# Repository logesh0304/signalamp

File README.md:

View this project on [CADLAB.io](https://cadlab.io/project/27638). 

# signalamp
 Signal amplifier for amplifying weak signals

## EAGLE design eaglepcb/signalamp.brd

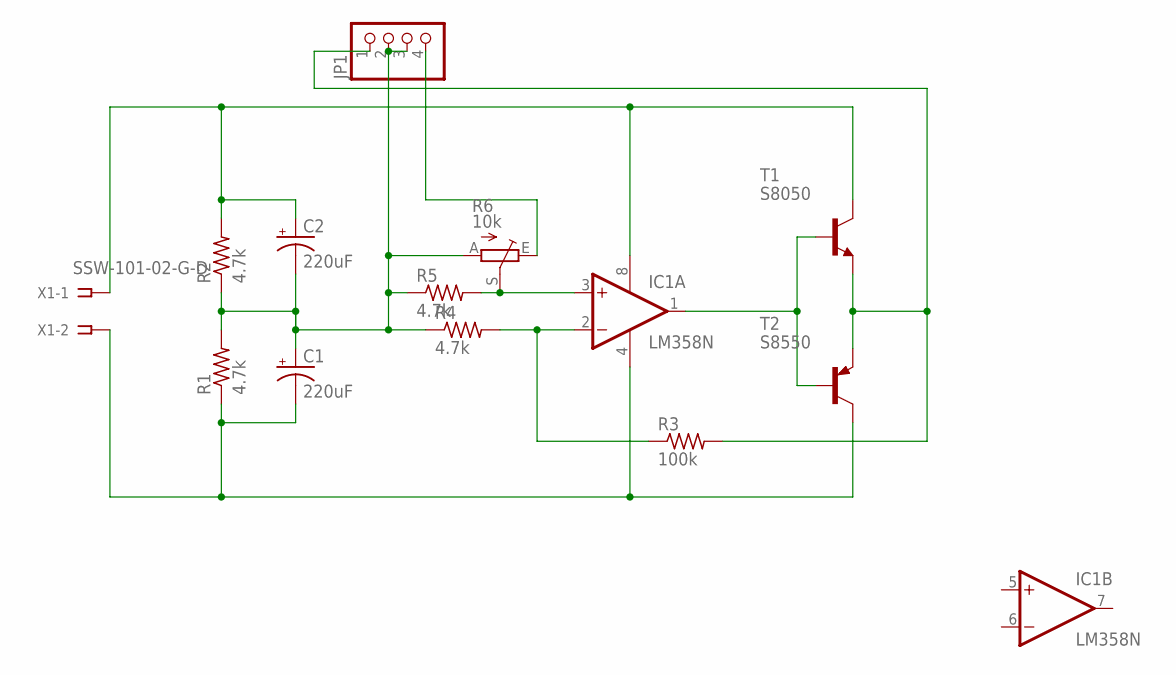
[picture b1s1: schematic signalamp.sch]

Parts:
C1, C2: 220uF; E2-5
IC1: LM358N; DIL08
JP1: PINHD-1X4; 1X04
R1, R2, R4: 4.7k; 0204/7
R3: 100k; 0207/5V
R5: 4.7k; 0207/2V
R6: 10k; S64W
T1: S8050; TO92-EBC
T2: S8550; TO92-EBC
X1: SSW-101-02-G-D

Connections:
unnamed: C2.+, IC1.8 (V+), R2.2, T1.C, X1.1
unnamed: C1.-, IC1.4 (V-), R1.1, T2.C, X1.2
unnamed: IC1.3 (+IN), R5.2, R6.S
unnamed: C1.+, C2.-, JP1.2, JP1.3, R1.2, R2.1, R4.1, R5.1, R6.A
unnamed: JP1.1, R3.2, T1.E, T2.E
unnamed: IC1.1 (OUT), T1.B, T2.B
unnamed: IC1.2 (-IN), R3.1, R4.2
unnamed: JP1.4, R6.E

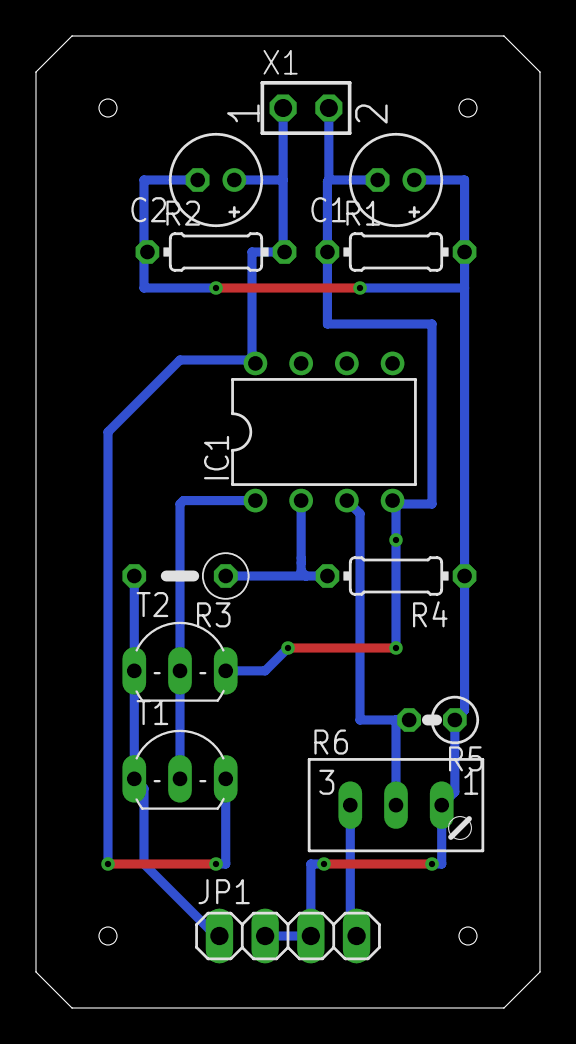
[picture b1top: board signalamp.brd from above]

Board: 2 copper layers, 28.0 x 54.0 mm, 13 parts (0 on the bottom side), 8 nets.

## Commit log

2024-01-08 added sources
2024-01-08 Backlink to CADLAB.io has been added.
